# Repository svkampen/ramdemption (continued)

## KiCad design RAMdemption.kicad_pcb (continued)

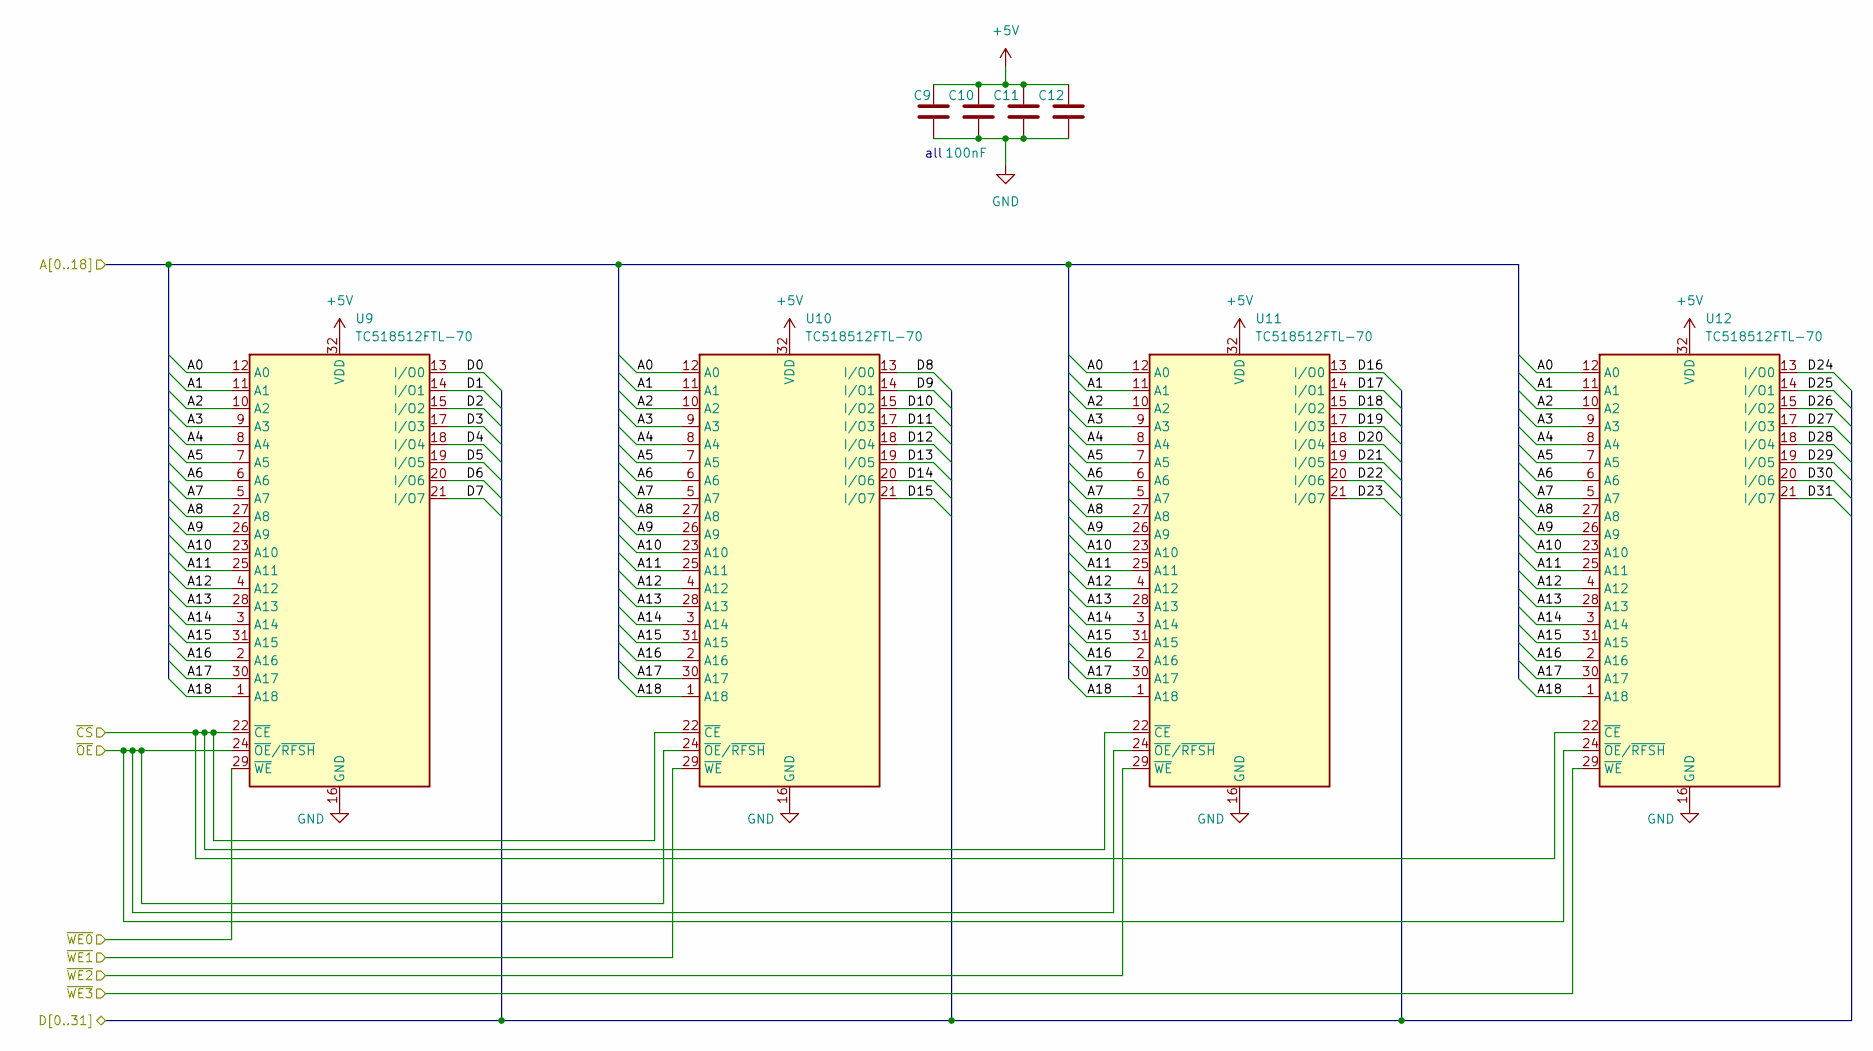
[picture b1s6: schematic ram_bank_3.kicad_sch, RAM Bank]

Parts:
C9, C10, C11, C12: 100nF; C_0805_2012Metric_Pad1.18x1.45mm_HandSolder
U9: TC518512FTL-70; TSOP-II-32_Data0
U10: TC518512FTL-70; TSOP-II-32_ReversedAddr
U11: TC518512FTL-70; TSOP-II-32_21.0x10.2mm_P1.27mm
U12: TC518512FTL-70; TSOP-II-NormalAddr-Data3

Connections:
+5V: C9.1, C10.1, C11.1, C12.1, U9.32 (VDD), U10.32 (VDD), U11.32 (VDD), U12.32 (VDD); also elsewhere on the board
/RAM Bank 1/A0: U9.12 (A0), U10.12 (A0), U11.12 (A0), U12.12 (A0); also elsewhere on the board
/RAM Bank 1/A1: U9.11 (A1), U10.11 (A1), U11.11 (A1), U12.11 (A1); also elsewhere on the board
/RAM Bank 1/A2: U9.10 (A2), U10.10 (A2), U11.10 (A2), U12.10 (A2); also elsewhere on the board
/RAM Bank 1/A3: U9.9 (A3), U10.9 (A3), U11.9 (A3), U12.9 (A3); also elsewhere on the board
/RAM Bank 1/A4: U9.8 (A4), U10.8 (A4), U11.8 (A4), U12.8 (A4); also elsewhere on the board
/RAM Bank 1/A5: U9.7 (A5), U10.7 (A5), U11.7 (A5), U12.7 (A5); also elsewhere on the board
/RAM Bank 1/A6: U9.6 (A6), U10.6 (A6), U11.6 (A6), U12.6 (A6); also elsewhere on the board
/RAM Bank 1/A7: U9.5 (A7), U10.5 (A7), U11.5 (A7), U12.5 (A7); also elsewhere on the board
/RAM Bank 1/A8: U9.27 (A8), U10.27 (A8), U11.27 (A8), U12.27 (A8); also elsewhere on the board
/RAM Bank 1/A9: U9.26 (A9), U10.26 (A9), U11.26 (A9), U12.26 (A9); also elsewhere on the board
/RAM Bank 1/A10: U9.23 (A10), U10.23 (A10), U11.23 (A10), U12.23 (A10); also elsewhere on the board
/RAM Bank 1/A11: U9.25 (A11), U10.25 (A11), U11.25 (A11), U12.25 (A11); also elsewhere on the board
/RAM Bank 1/A12: U9.4 (A12), U10.4 (A12), U11.4 (A12), U12.4 (A12); also elsewhere on the board
/RAM Bank 1/A13: U9.28 (A13), U10.28 (A13), U11.28 (A13), U12.28 (A13); also elsewhere on the board
/RAM Bank 1/A14: U9.3 (A14), U10.3 (A14), U11.3 (A14), U12.3 (A14); also elsewhere on the board
/RAM Bank 1/A15: U9.31 (A15), U10.31 (A15), U11.31 (A15), U12.31 (A15); also elsewhere on the board
/RAM Bank 1/A16: U9.2 (A16), U10.2 (A16), U11.2 (A16), U12.2 (A16); also elsewhere on the board
/RAM Bank 1/A17: U9.30 (A17), U10.30 (A17), U11.30 (A17), U12.30 (A17); also elsewhere on the board
/RAM Bank 1/A18: U9.1 (A18), U10.1 (A18), U11.1 (A18), U12.1 (A18); also elsewhere on the board
/RAM Bank 1/D0: U9.13 (I/O0); also elsewhere on the board
/RAM Bank 1/D1: U9.14 (I/O1); also elsewhere on the board
/RAM Bank 1/D2: U9.15 (I/O2); also elsewhere on the board
/RAM Bank 1/D3: U9.17 (I/O3); also elsewhere on the board
/RAM Bank 1/D4: U9.18 (I/O4); also elsewhere on the board
/RAM Bank 1/D5: U9.19 (I/O5); also elsewhere on the board
/RAM Bank 1/D6: U9.20 (I/O6); also elsewhere on the board
/RAM Bank 1/D7: U9.21 (I/O7); also elsewhere on the board
/RAM Bank 1/D8: U10.13 (I/O0); also elsewhere on the board
/RAM Bank 1/D9: U10.14 (I/O1); also elsewhere on the board
/RAM Bank 1/D10: U10.15 (I/O2); also elsewhere on the board
/RAM Bank 1/D11: U10.17 (I/O3); also elsewhere on the board
/RAM Bank 1/D12: U10.18 (I/O4); also elsewhere on the board
/RAM Bank 1/D13: U10.19 (I/O5); also elsewhere on the board
/RAM Bank 1/D14: U10.20 (I/O6); also elsewhere on the board
/RAM Bank 1/D15: U10.21 (I/O7); also elsewhere on the board
/RAM Bank 1/D16: U11.13 (I/O0); also elsewhere on the board
/RAM Bank 1/D17: U11.14 (I/O1); also elsewhere on the board
/RAM Bank 1/D18: U11.15 (I/O2); also elsewhere on the board
/RAM Bank 1/D19: U11.17 (I/O3); also elsewhere on the board
/RAM Bank 1/D20: U11.18 (I/O4); also elsewhere on the board
/RAM Bank 1/D21: U11.19 (I/O5); also elsewhere on the board
/RAM Bank 1/D22: U11.20 (I/O6); also elsewhere on the board
/RAM Bank 1/D23: U11.21 (I/O7); also elsewhere on the board
/RAM Bank 1/D24: U12.13 (I/O0); also elsewhere on the board
/RAM Bank 1/D25: U12.14 (I/O1); also elsewhere on the board
/RAM Bank 1/D26: U12.15 (I/O2); also elsewhere on the board
/RAM Bank 1/D27: U12.17 (I/O3); also elsewhere on the board
/RAM Bank 1/D28: U12.18 (I/O4); also elsewhere on the board
/RAM Bank 1/D29: U12.19 (I/O5); also elsewhere on the board
/RAM Bank 1/D30: U12.20 (I/O6); also elsewhere on the board
/RAM Bank 1/D31: U12.21 (I/O7); also elsewhere on the board
/~WE0: U9.29 (~WE); also elsewhere on the board
/~WE1: U10.29 (~WE); also elsewhere on the board
/~WE2: U11.29 (~WE); also elsewhere on the board
/~WE3: U12.29 (~WE); also elsewhere on the board
GND: C9.2, C10.2, C11.2, C12.2, U9.16 (GND), U10.16 (GND), U11.16 (GND), U12.16 (GND); also elsewhere on the board
~CS4: U9.22 (~CE), U10.22 (~CE), U11.22 (~CE), U12.22 (~CE); also elsewhere on the board
~OE: U9.24 (~OE/~RFSH), U10.24 (~OE/~RFSH), U11.24 (~OE/~RFSH), U12.24 (~OE/~RFSH); also elsewhere on the board

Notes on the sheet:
all

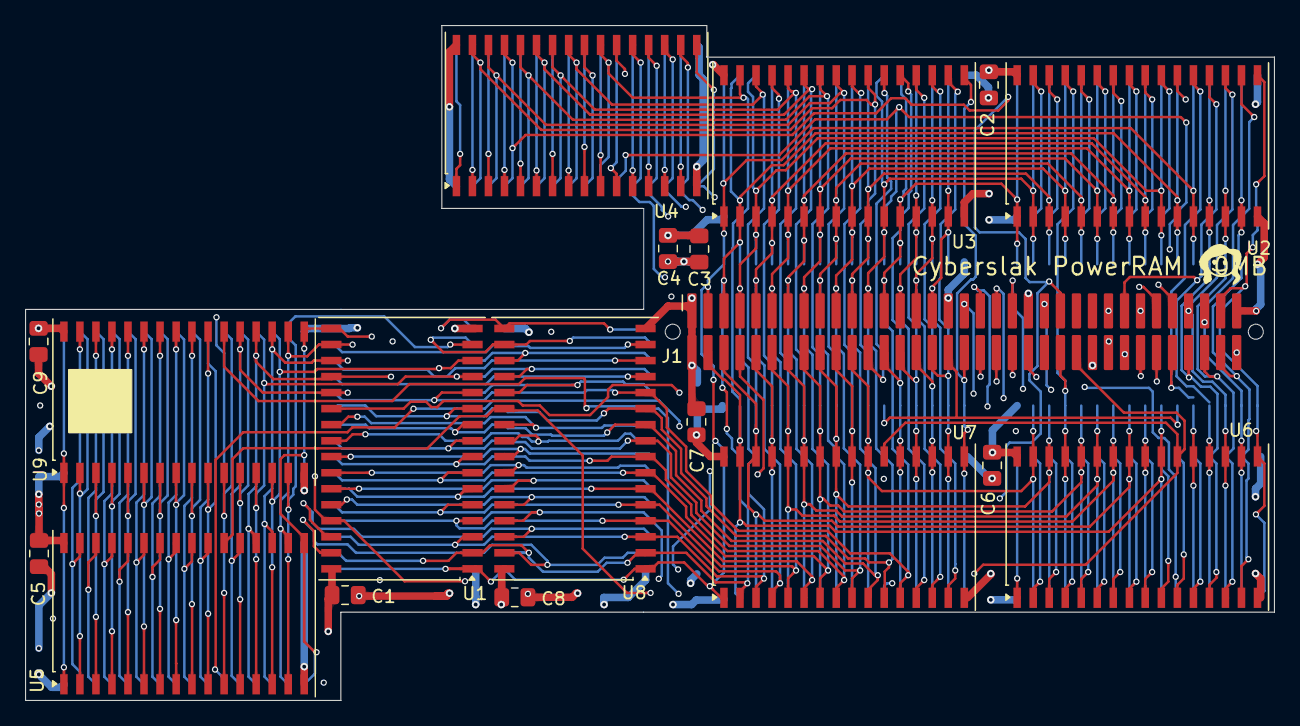
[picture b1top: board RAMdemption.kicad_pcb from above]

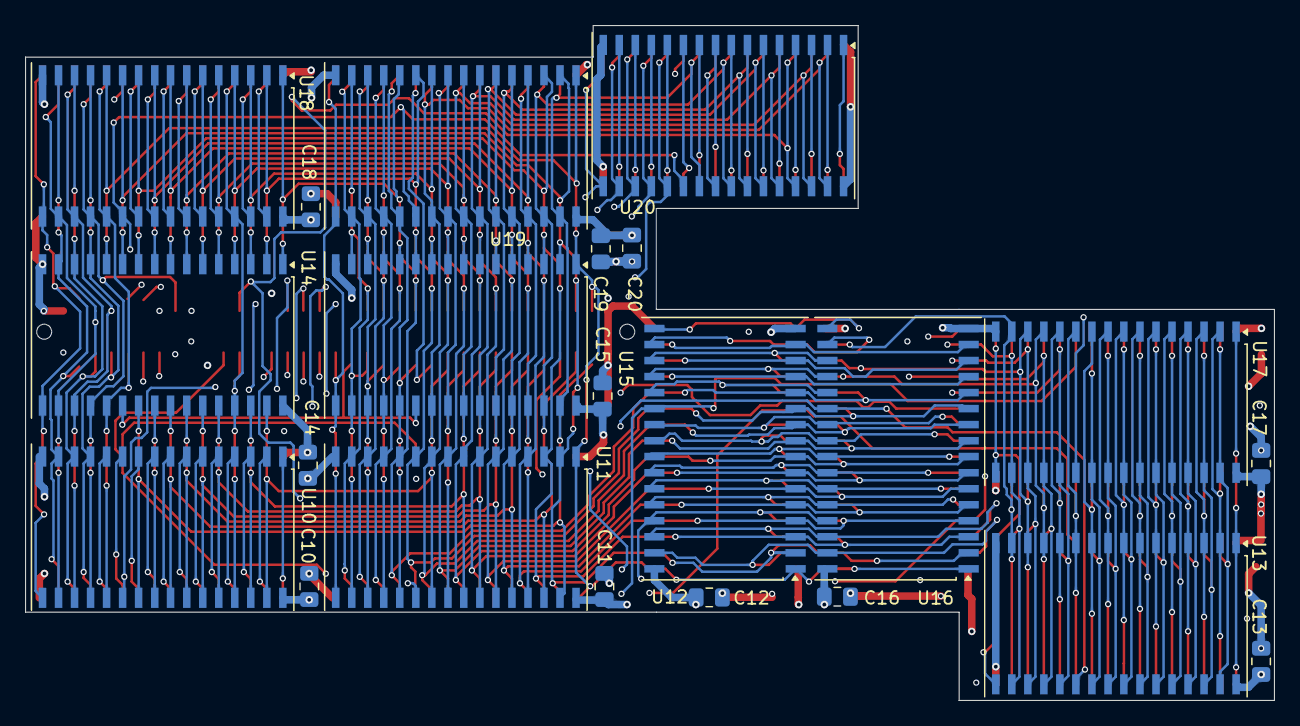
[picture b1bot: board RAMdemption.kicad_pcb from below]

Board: 6 copper layers, 99.0 x 53.5 mm, 41 parts (22 on the bottom side), 63 nets.

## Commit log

2025-04-15 archived files (pre-version control)
2025-04-15 preliminary power routing
2025-04-15 fix up positions of U10, U14, U18 etc
2025-04-17 progress!
2025-04-17 version of connector without mounting holes
2025-04-17 shuffle around files
2025-04-17 lots of address routing (with some tricks)
2025-04-17 addresses done?!
2025-04-18 just fifteen left unrouted
2025-04-19 routed all except UUW data lines
2025-04-19 routing complete
2025-04-20 various improvements
2025-04-28 fix drc
2025-04-28 redo cap placement
2025-04-28 six-layer stackup
2025-04-30 mostly rework
2025-05-01 finish
2025-05-02 add board name, 3d connector model
2025-05-03 pcb page size
2025-05-03 prepare for production
2025-05-03 update gitignore
2025-05-03 README
2025-05-03 update 3d render
2025-05-03 remove old files
